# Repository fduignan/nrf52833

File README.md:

# nrf52833
Various projects involving the NRF52833 from Nordic Semiconductor.
The DublinMaker2022 project contains firmware for the Dublin Maker 2022 badge.  
It includes a number of games and badge to badge communications.  More details
over at https://ioprog.com

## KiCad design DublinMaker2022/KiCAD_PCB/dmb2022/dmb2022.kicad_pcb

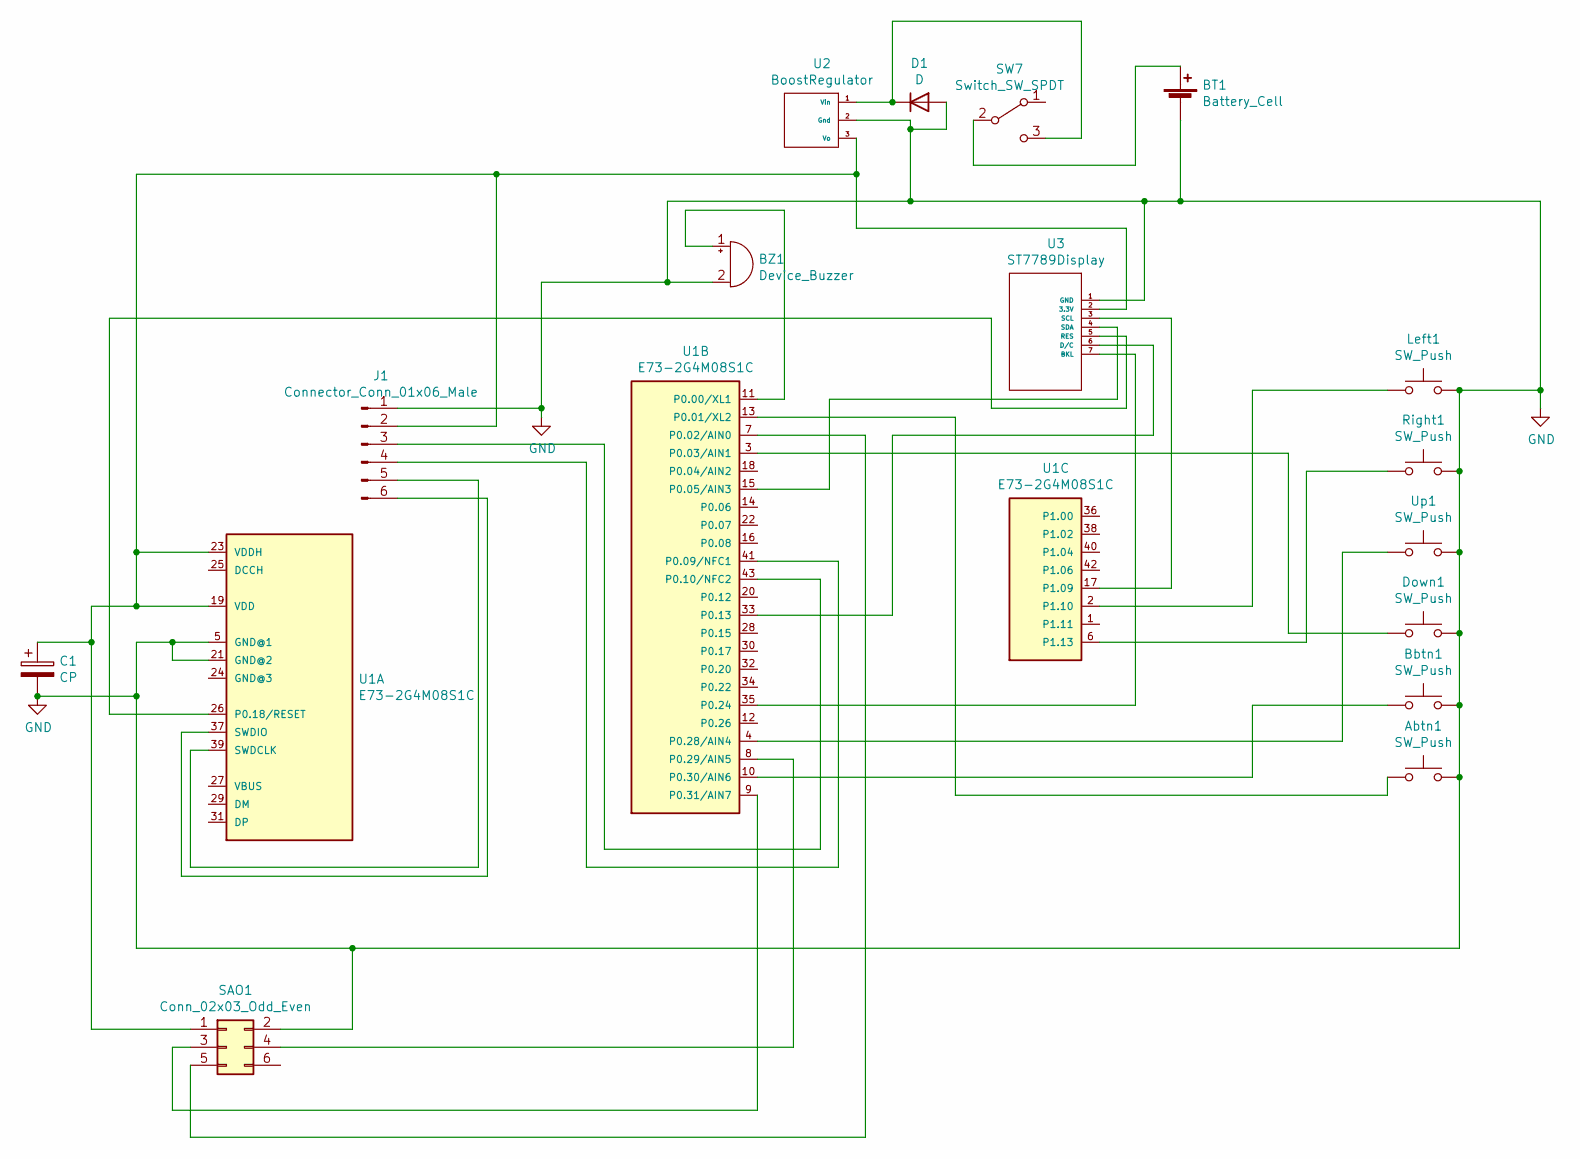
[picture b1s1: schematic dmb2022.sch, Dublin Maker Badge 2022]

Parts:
Abtn1: SW_Push; ST7789Display
BT1: Battery_Cell; BatteryHolder_Keystone_2460_1xAA
BZ1: Device_Buzzer; Buzzer_TDK_PS1240P02BT_D12.2mm_H6.5mm
Bbtn1: SW_Push; SW_PUSH_6mm
C1: CP; CP_Radial_D10.0mm_P5.00mm
D1: D; D_DO-34_SOD68_P7.62mm_Horizontal
Down1: SW_Push; SW_PUSH_6mm
J1: Connector_Conn_01x06_Male; PinHeader_1x06_P2.54mm_Vertical
Left1: SW_Push; SW_PUSH_6mm
Right1: SW_Push; SW_PUSH_6mm
SAO1: Conn_02x03_Odd_Even; IDC-Header_2x03_P2.54mm_Vertical
SW7: Switch_SW_SPDT; PinHeader_1x03_P2.54mm_Vertical
U1: E73-2G4M08S1C
U2: BoostRegulator; PinHeader_1x03_P2.54mm_Vertical
U3: ST7789Display; PinHeader_1x07_P2.54mm_Vertical
Up1: SW_Push; SW_PUSH_6mm

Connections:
GND: Abtn1.2, BT1.2 (-), BZ1.2 (+), Bbtn1.2, C1.2, D1.2 (A), Down1.2, J1.1, Left1.2, Right1.2, SAO1.2, U1.5 (GND@1), U1.21 (GND@2), U2.2 (Gnd), U3.1 (GND), Up1.2
unnamed: Abtn1.1, U1.13 (P0.01/XL2)
unnamed: BT1.1 (+), SW7.2 (B)
unnamed: BZ1.1 (-), U1.11 (P0.00/XL1)
unnamed: Bbtn1.1, U1.10 (P0.30/AIN6)
unnamed: C1.1, J1.2, SAO1.1, U1.19 (VDD), U1.23 (VDDH), U2.3 (Vo), U3.2 (3.3V)
unnamed: D1.1 (K), SW7.3 (C), U2.1 (Vin)
unnamed: Down1.1, U1.3 (P0.03/AIN1)
unnamed: J1.3, U1.43 (P0.10/NFC2)
unnamed: J1.4, U1.41 (P0.09/NFC1)
unnamed: J1.5, U1.39 (SWDCLK)
unnamed: J1.6, U1.37 (SWDIO)
unnamed: Left1.1, U1.2 (P1.10)
unnamed: Right1.1, U1.6 (P1.13)
unnamed: SAO1.3, U1.9 (P0.31/AIN7)
unnamed: SAO1.4, U1.8 (P0.29/AIN5)
unnamed: SAO1.5, U1.7 (P0.02/AIN0)
unnamed: U1.4 (P0.28/AIN4), Up1.1
unnamed: U1.15 (P0.05/AIN3), U3.4 (SDA)
unnamed: U1.17 (P1.09), U3.3 (SCL)
unnamed: U1.26 (P0.18/RESET), U3.5 (RES)
unnamed: U1.33 (P0.13), U3.6 (D/C)
unnamed: U1.35 (P0.24), U3.7 (BKL)

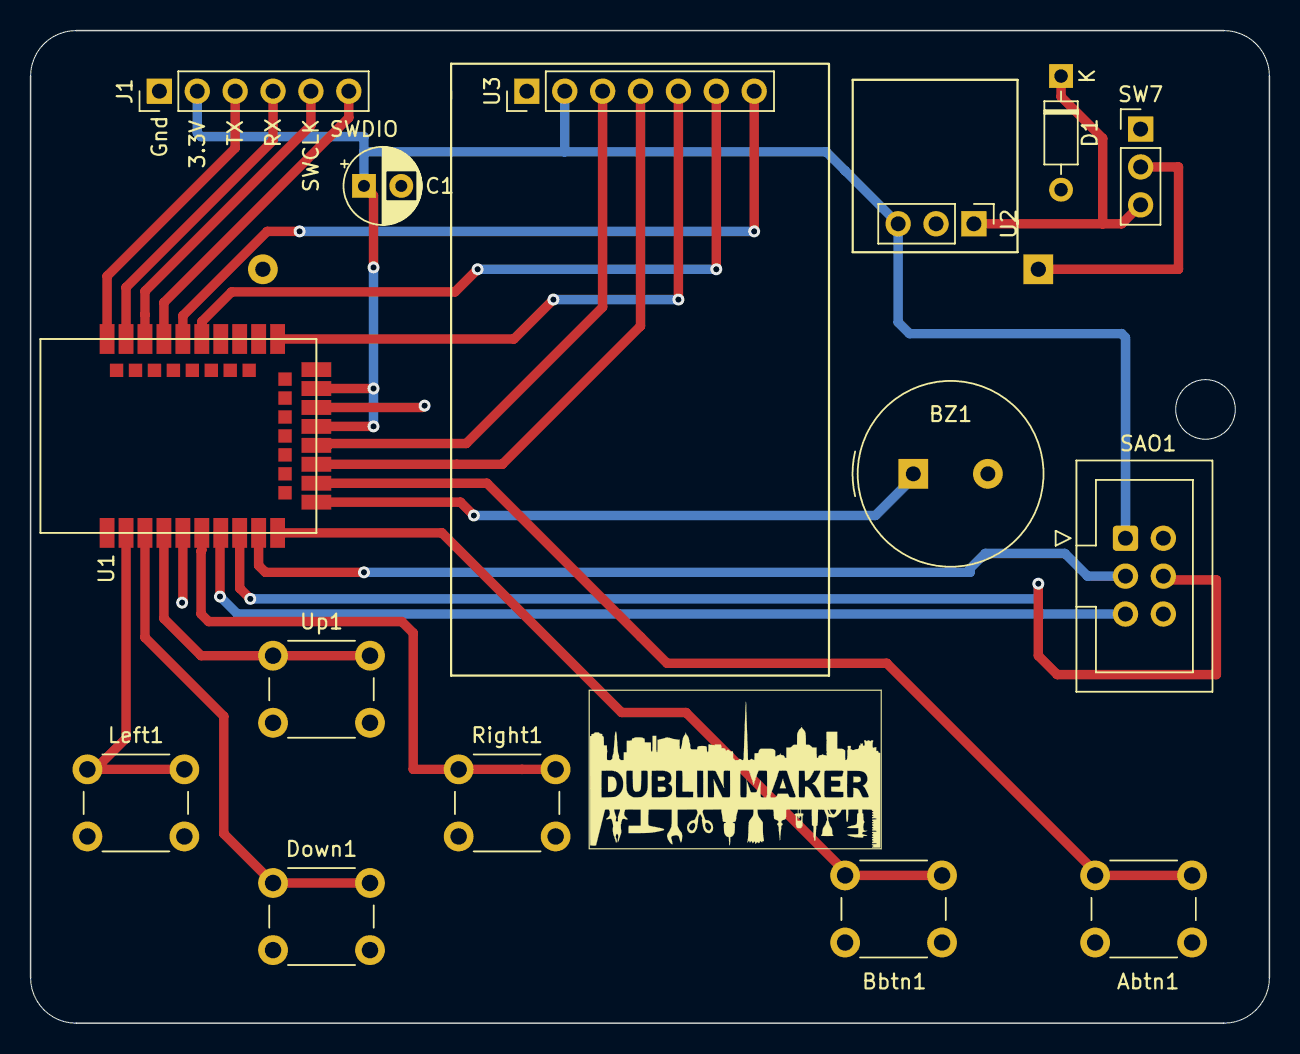
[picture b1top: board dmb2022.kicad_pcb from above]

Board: 2 copper layers, 83.1 x 66.5 mm, 16 parts (1 on the bottom side), 23 nets.

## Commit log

2022-03-13 First commit to github
2022-07-24 First release of badge firmware as used in Dublin Maker on 23rd July 2022
2022-07-24 changed readme
2022-07-27 Added KiCAD files
2022-09-26 Lots of changes to accommodate Zephyr 3.1. Mesh comms not working yet
